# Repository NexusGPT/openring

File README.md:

<h1 align="center">OpenRing</h1>

<p align="center">
  <b>An open-source ring that records your meetings.</b><br>
  One joystick, a small screen, two microphones and its own storage, in a ring you wear on your index finger.
</p>

<p align="center">
  <a href="#what-it-is">What it is</a> ·
  <a href="#where-the-project-stands">Status</a> ·
  <a href="#inside-the-ring">Inside</a> ·
  <a href="#the-software">Software</a> ·
  <a href="#what-is-in-this-repository">Files</a> ·
  <a href="#check-it-yourself">Checks</a> ·
  <a href="#licence">Licence</a>
</p>

---

## What it is

OpenRing is the complete design of a meeting recorder that you wear as a ring:

- **Press and hold the joystick for one second** and the ring records. Hold again and it stops. Nothing else starts a recording: no voice trigger, no phone command, no always-on listening.
- **The screen shows that it records.** A red dot and a timer stay lit for the whole recording, so the people around you can see it.
- **The audio stays on the ring.** It is stored on the ring's own 4 GB memory and moves to your computer through the charging case over USB.
- **It also controls your devices.** Paired with up to three devices, the ring works as a Bluetooth keyboard, media remote and pointer, and it shows iPhone notifications.

Everything needed to build it is here: 3D models, wiring, parts lists, drawings, the assembly order, the behaviour specification and the ring's software with its tests.

## Where the project stands

> **This is a design, not a product. No ring has been built yet.**
> Every claim below says how it was checked. Nothing here has run on real hardware.
> State of 14 November 2026: an intermediate release, pushed while the work below is open.

| Part | State | How it was checked |
|---|---|---|
| Ring exterior, 7 sizes (US 7 to 13) | being rebuilt on the thin block (3.20 mm) for a flat cover glass over a custom full-face screen panel; a taller 4.17 mm exterior for a stock screen is kept as a fallback | 3D models per size, measured by script |
| Inside of the ring | designed for the thin block with a stock screen; the rebuild for the custom panel and the flat glass is in work | fit check per size on the earlier model |
| Charging case | designed; its fit to the ring with the flat glass is not redone yet | fit check against the earlier ring models |
| Circuit boards (17: the ring's main board, 14 band circuits for 7 sizes, 2 case boards) | **routed**. The main board is the thin ring's: screen connector on the under face, no soldered part on the screen face. The board for the 4.17 mm fallback is kept in `design/ecad/ring/pcb/fallback-417` | design rules check: 0 violations and 0 unconnected on each board; the main board's 8 limits for the antenna, crystal and USB lines are met |
| Wiring list (`design/wiring/product-wiring.csv`) | written: 66 conductors, each with both ends, its carrier and its cut length per size | a check compares the list with the boards and the netlists; an independent review found the list true (67 of 67 lines) |
| Joint table and build guide (`design/mfg/assembly/`) | written: 99 joints | **an independent review of 13 November failed the guide on 3 points, listed below; 1 is open, and the guide is behind the thin ring's main board** |
| Circuit simulation (`design/sim/circuit/`) | 13 tests pass | each test has a pass line written before the run and a faulty copy that must fail |
| Ring software: core, paired devices, control, iPhone services, screens, Android relay | written | simulated on the ring's chip model with real Bluetooth encryption |
| Ring software: recorder parts (microphones, storage, USB transfer, power) | written against simulated drivers | the full test run passes on the simulated board (732 of 732 test cases on each of two simulated targets); two independent reviews, the second passed it |
| Ring software: the real ring's board files | written: it builds for the real ring's board with the real drivers, and in a second form without the debug port | every chip pin is checked against the circuit's connection list, with deliberately wrong copies that must fail; four independent reviews, the fourth passed it; **nothing has run on hardware** (`firmware/docs/step7-report.md`) |
| Ring software: the screen's panel driver, the joystick's driver | **not written** | the panel driver needs the panel maker's answer |
| A working ring | **does not exist** | needs a development kit bench first, see `design/bench/` |

An independent review found three faults that stop a build from the files. Two are fixed in the guide; the first is open. They are written up in `design/wiring/wiring-review-4.md`:

1. **The body files are behind.** The body drawings still show the earlier block, without the two side slits the ribbons pass through and without the pocket of the custom screen panel. Open.
2. **Two ground joints per ribbon cannot be told apart by a meter.** The decision is to treat them as a spare pair; the guide now says what its test proves. Fixed.
3. **No test proved the two thermistor joints of the case.** A resistance check is added to the case board's tests. Fixed.

Four values need a measurement on the first built ring: the antenna match, the accuracy of the 32 MHz clock, the case's input current while a ring charges, and USB through the case's spring pins (`design/ecad/risk-review.md`).

## How you use it

<table>
  <tr>
    <td width="50%"></td>
    <td width="50%"></td>
  </tr>
</table>

The ring has **one control**: a round five-way joystick on the side of the band, under your thumb.

| You do | The ring does |
|---|---|
| Hold the centre for 1 second | starts a recording; hold again to stop |
| Short press while recording | marks a highlight |
| Push up, down, left, right | moves through the menu |
| Open a control mode | sends keys to the active device: media, slides, pointer, or accept and decline |

A vibration motor confirms the start and the stop.

## Inside the ring

| | |
|---|---|
| **Size** | block 29.3 x 14.75 x 3.85 mm on a band 8.0 mm wide and 2.6 mm thick |
| **Body** | titanium grade 5, gloss black |
| **Screen** | 0.95 inch AMOLED, 120 x 240 pixels, under a formed cover glass |
| **Main chip** | Nordic nRF54LM20A (Bluetooth LE) |
| **Power chip** | Nordic nPM1304 |
| **Microphones** | 2 x Knowles SPK0641HT4H-1, 16 kHz, 16 bit, two channels, stored raw |
| **Storage** | 4 GB, on the ring |
| **Battery** | a custom curved cell inside the band, 17.6 to 31.9 mAh depending on ring size |
| **Recording time** | 4.3 to 7.8 hours by ring size (calculated, not measured) |
| **Feedback** | vibration motor |
| **Charging** | 4 pads on the inside of the band, touched by 4 spring pins in the case |
| **Weight** | not known yet; body, joystick and motor alone come to 4.6 to 5.4 g |

The exploded view is an illustration from the project's own models. The reference is always the model and the parts list in `design/`.

## The screen

These 21 pictures come from the ring's own screen code. The code draws each screen on a simulated display, and a test reads the picture back from the display memory and checks it. The pictures are in `design/software/os/screens/`.

**Limit:** no real panel has shown them. The driver for the ring's panel is not written, because no ready driver exists for that panel.

## The charging case

<table>
  <tr>
    <td width="50%"></td>
    <td width="50%"></td>
  </tr>
</table>

A soft cube of 45.4 x 45.9 x 41.4 mm with a lid that swivels aside. The ring sits around a centre post. Four spring pins on the post touch the pads inside the band. The case charges the ring from its own 700 mAh cell and moves the recordings to a computer over USB-C.

One post holds all seven ring sizes. The fit check places the real ring model of every size in the case and measures every pin against its pad.

## The software

The ring runs a small firmware on Zephyr and the nRF Connect SDK. It is written to be proven without hardware: every step ends with tests on a simulated ring chip, and with deliberately broken copies that must fail.

| Step | What it does | State |
|---|---|---|
| 1. Core | the state machine and the joystick gestures of the behaviour specification | done, tests pass |
| 2. Devices and control | passkey pairing, three paired devices, keyboard, media and pointer control | done, tests pass |
| 3. iPhone | notifications with their actions, track and media commands, time | done, tests pass |
| 4. Screens | the 21 screens, the menu, the notification list, the control and device screens | done, tests pass |
| 5. Android relay | a small service on the ring that takes notifications from a helper app, and the written specification for that app | done, tests pass |
| 6. Recorder | microphones, storage, USB transfer, power, factory tests, against simulated drivers | written and reviewed; the fixes of the last review are in, their full test run pending |
| 7. Board | the real ring's board files | not started |

What works per device, by design:

| Device | Control by the ring | Notifications on the ring |
|---|---|---|
| iPhone | yes | yes |
| Android | yes | yes on the ring side; needs a helper app on the phone (specified in `design/software/os/android-helper-spec.md`, not built) |
| Mac | yes | no supported way was found |

**Honest limit:** the tests use stand-in devices written for this project. Nothing has been tried against a real iPhone, Android phone or Mac.

## What is in this repository

| Folder | What it holds |
|---|---|
| `requirements.md` | what the ring must do, with every later change and its reason |
| `design/architecture.md` | the design record: every decision, in order |
| `design/bom.csv` | the ring's parts list, with maker part numbers |
| `design/ecad/` | wiring diagram, netlist and circuit board files (KiCad) |
| `design/wiring/` | every conductor of the product in one list, its drawing, the decisions and the independent wiring reviews |
| `design/sim/` | the circuit simulation bench |
| `design/mech/` | the inside model of the ring and its fit check |
| `design/look/` | the exterior model, one file per ring size |
| `design/mfg/` | maker files (STEP, STL), drawings, one specification page per custom part, the assembly order |
| `design/case/` | the charging case: model, parts list, wiring, fit check |
| `design/firmware.md` | the behaviour specification the software follows |
| `design/bench/` | the plan for a desk prototype from development kits |
| `design/review/` | three independent reviews of the design, with their findings |
| `firmware/` | the ring's software, its tests and the build scripts |
| `explorer/` | a browser app to look through the design |
| `LICENSES/`, `LICENSE.md`, `NOTICE.md` | the licences and the third-party notice |

Maker datasheets are not included. `design/datasheets/README.md` lists each bought part with its maker and part number.

## Check it yourself

The design ships with its own checks. Each one reads the design files and fails when they disagree with each other.

These run from this repository alone:

```sh
python3 design/tools/check_bom.py          # parts list against the wiring and the model
python3 design/mfg/tools/check_docs.py     # maker specification pages
python3 design/case/check_case_docs.py     # case documents
python3 tools/check_public.py              # this repository holds no private or third-party file
```

These four also read the makers' own datasheets, which are not in this repository (their makers own them). They stop with "cannot read" or "no file" until you download the documents listed in `design/datasheets/README.md` and put them where each check names them:

```sh
python3 design/ecad/ring/check_netlist.py         # wiring rules, against the makers' pin tables
python3 design/firmware-check.py                  # behaviour specification
python3 design/mfg/assembly/check_assembly.py     # assembly order and its citations
python3 design/bench/check_bench.py design/bench/bench-plan.md design/bom.csv
```

All seven passed on the full project before the maker documents were taken out for this release.

The 3D model checks (`design/mech/thin/check_thin.py`, `design/case/case_check.py`) need the Python package `build123d` and take 20 to 60 minutes each.

To build and test the software, read `firmware/README.md`. It needs Linux and Nordic's toolchain; the chip simulation does not run on macOS.

## What is not done

- The first fault above (the body files) is open.
- The inside model, the body maker files, the case fit and the pictures of this page still show the thin block with a stock screen under a formed glass (3.85 mm on this page's table). The design moves to a custom screen panel that fills the face, under a flat glass, on the same thin block. The requirement page for panel makers is `design/mfg/specs/screen-panel-custom.md`; no maker has answered.
- The build guide and its joint table still describe a second soldering pass for the main board's screen face. The thin ring's board has no soldered part there, so that pass is no longer needed; the guide's rework is open.
- No part has been ordered, measured or assembled.
- The spring pin of the case and the thin walls of its pin holder are not confirmed by a maker.
- Battery life, radio range, sound quality, water resistance and weight are calculated or unknown. None is measured.
- The software has no panel driver and no board files for the real ring yet. The Android helper app is specified and not built.

If you build any of it, measure something, or find a mistake, open an issue. That is why the design is public.

## Licence

OpenRing is open hardware and open software:

| What | Licence |
|---|---|
| Hardware design: 3D models, wiring, circuit board, parts lists, drawings | CERN-OHL-S 2.0 (share-alike) |
| Software: `firmware/`, `explorer/` and every script | Apache 2.0 |
| Documents and pictures | CC BY 4.0 |

The licence texts are in `LICENSES/`. Details per folder are in [LICENSE.md](LICENSE.md). Third-party software and parts keep their own licences, see [NOTICE.md](NOTICE.md).

## About the name

This project is not related to other projects with a similar name, among them the research app repository `thuhci/OpenRing` and the hardware project `stawiski/open-ring`.

## How this was made

The pictures on this page are rendered from the project's own 3D models. The design files, the checks and the software were produced with AI assistance and reviewed by independent AI reviewers; their reports are in `design/review/` and `firmware/docs/`. Treat every number as a design value until someone measures it.

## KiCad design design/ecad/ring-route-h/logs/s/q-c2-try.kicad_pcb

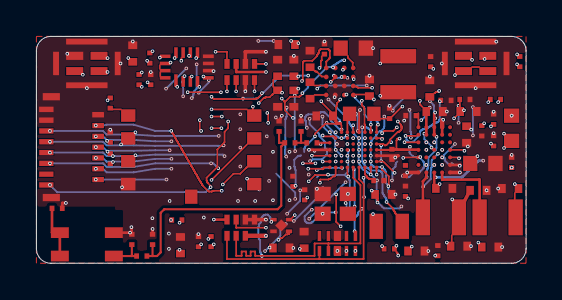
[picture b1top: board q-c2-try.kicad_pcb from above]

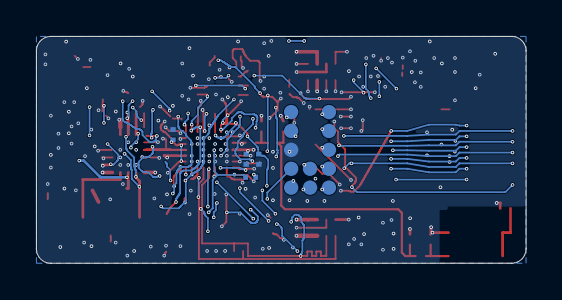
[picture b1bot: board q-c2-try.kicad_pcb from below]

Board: 4 copper layers, 27.2 x 12.6 mm, 99 parts (16 on the bottom side), 84 nets.

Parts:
ANT1: 2450AT18D0100001E; ANT_Johanson_2450AT18D0100001E_3.2x1.6
C1, C2, C5, C61, C72, C80, C81, C82: 100nF; Chip_0201
C3: 1.2pF; Chip_0201
C4, C22, C25, C74, C75, C78, C79, C83, C90: 10uF; Chip_0402
C6: 4.7uF; Chip_0201
C7, C10, C14: 2.2uF; Chip_0201
C11, C21, C26, C27, C84: 4.7uF; Chip_0402
C12: 0.5pF; Chip_0201
C13, C89: DNP; Chip_0201
C23, C60, C85: 2.2uF; Chip_0402
C24, C88: 10uF; Chip_0603
C28, C29: 22uF; Chip_0402
C31, C32: 1uF; Chip_0201
C35, C36: 1nF C0G; Chip_0402
C71: 1.0uF 25V; Chip_0402
C73: 1.0uF; Chip_0201
C76, C77: 1.0nF; Chip_0201
C86, C87: 1.0uF; Chip_0402
FB1: 120R@100MHz; Chip_0201
J1: FH35C-15S-0.3SHW(50); FPC_Hirose_FH35C-15S-0.3SHW
J_BAND_A: flex tail A (joystick side) 8 pads; J_BAND_A_BOARD
J_BAND_B: flex tail B (other side) 7 pads; J_BAND_B_BOARD
L1: 4.7uH; L_TDK_MLZ1608_1.6x0.8
L2: 3.6nH; Chip_0201
L3: 4.7nH; Chip_0201
L4: 3.3nH; Chip_0201
L10, L71, L72: 2.2uH; L_Murata_1269AS-H_2.5x2.0
LT1: 0R; Chip_0201
R1: 2.2R; Chip_0603
R2: 220R; Chip_0201
R31, R32, R61: 100R; Chip_0201
R57, R58: 4.7k; Chip_0201
R60, R63, R64, R65, R71: 47k; Chip_0201
R62, R66: 100k; Chip_0201
R72: 150k; Chip_0201
R73: 330k; Chip_0201
TP1, TP3, TP4, TP5, TP6, TP12, TP14, TP15, TP17, TP18, TP19, TP21: pad; TESTPAD_0.8
U1: nRF54LM20A; WLCSP-61_nRF54LM20A-CAAA
U2: nPM1304; WLCSP-35_nPM1304-CAAA
U3: CSNP32GCR01-BOW; LGA-9_CSNP32GCR01-BOW_8.0x6.2
U4: SGM38046; WLCSP-16_SGM38046_2.0x2.0_P0.5
U5, U6: SPK0641HT4H-1; LGA-8_Knowles_SPK0641HT4H-1_3.0x4.0
U9: TPD4E05U06; USON-10_TPD4E05U06DQA
U10: SN74AXC4T774; UQFN-16_SN74AXC4T774RSV_1.8x2.6
U11: TLV75530P 3.0V; X2SON-4_TLV755xxPDQN_1.0x1.0
X1: 32MHz; XTAL_Kyocera_CX2016DB_2.0x1.6
X2: 32.768kHz; XTAL_TXC_9HT11_2.0x1.2

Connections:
ANT1_NODE: L2.1, U1.C1
ANT2_NODE: C3.1, L2.2, L3.1
ANT3_NODE: C12.1, C89.1, L3.2, L4.1
ANT_TRIM: ANT1.2, ANT1.3, LT1.1
BTN_REC: J_BAND_A.5, U1.H2
DBG_TX: TP1.1, U1.B4
DCC: L1.1, U1.A5
DECA: C7.1, C14.1, FB1.2, U1.A8, U1.B2
DECD: C6.1, FB1.1, L1.2, U1.A6
ELVDD: C25.1, J1.2, U4.D3
ELVSS: C28.1, C29.1, J1.1, U4.D4
GND: ANT1.4, C1.2, C2.2, C3.2, C4.2, C5.2, C6.2, C7.2, C10.2, C11.2, C12.2, C13.2, C14.2, C21.2, C22.2, C24.2, C25.2, C26.2, C27.2, C28.2, C29.2, C31.2, C32.2, C35.2, C36.2, C60.2, C61.2, C71.2, C72.2, C73.2, C74.2, C75.2, C76.2, C77.2, C78.2, C79.2, C80.2, C81.2, C82.2, C83.2, C84.2, C85.2, C86.2, C87.2, C88.2, C89.2, C90.2, J1.13, J1.14, J1.15, J1.MP, J_BAND_A.6, J_BAND_A.8, J_BAND_B.2, J_BAND_B.7, LT1.2, R2.2, R62.2, R66.2, R71.2, R72.2, R73.2, TP18.1, U1.A7, U1.D3, U1.E1, U1.F10, U2.A6, U2.A7, U2.E7, U3.4, U4.A3, U4.B2, U4.B3, U5.3, U5.5, U5.6, U5.7, U5.8, U6.5, U6.6, U6.7, U6.8, U9.3, U9.8, U10.6, U10.7, U10.8, U11.2, U11.5, X1.2
JOY_DOWN: J_BAND_A.2, U1.G2
JOY_LEFT: J_BAND_A.3, U1.G1
JOY_RIGHT: J_BAND_A.4, U1.G10
JOY_UP: J_BAND_A.1, U1.H1
LCD_CS: J1.9, U1.F7
LCD_DCX: J1.11, U1.G7
LCD_MOSI: J1.12, U1.G8
LCD_RST: J1.8, U1.H5
LCD_SCK: J1.10, U1.G9
LCD_TE: J1.7, U1.F4
MIC1_DATA: R31.1, U5.1
MIC2_DATA: R32.1, U6.1
MIC_A_CLK: U1.F1, U5.2, U6.2
MIC_A_DATA: R31.2, R32.2, U1.F2
MIC_B_DATA: TP21.1, U1.D7
MOTOR: R61.1, U1.F6
MOT_EN: R61.2, R62.1, U11.3
NRESET: TP5.1, U1.E2
NTC: J_BAND_B.3, U2.D3
OLED_PWR_EN: R66.1, U1.F9, U4.C2
PMIC_INT: U1.D8, U2.D6
PMIC_SCL: R58.1, U1.E7, U2.E3
PMIC_SDA: R57.1, U1.B8, U2.E5
RF_FEED: ANT1.1, C13.1, L4.2
SDC_CS: R65.1, U3.2, U10.10
SDC_MISO: R60.1, U3.6, U10.9
SDC_MOSI: U3.5, U10.11
SDC_SCK: U3.3, U10.12
SD_CS: U1.D9, U10.3
SD_DAT1: R63.1, U3.7
SD_DAT2: R64.1, U3.1
SD_MISO: U1.D10, U10.4
SD_MOSI: U1.B10, U10.2
SD_SCK: U1.A9, U10.1
SGM_AVDD: C26.1, U4.D2
SGM_AVIN: C22.1, U4.A2
SGM_C1N: C23.2, U4.B4
SGM_C1P: C23.1, U4.A4
SGM_SW1: L10.1, U4.B1
SGM_SW2: L10.2, U4.C1
SGM_VON: C27.1, U4.C4
SGM_VOUT: C24.1, U4.D1
SHPHLD: TP19.1, U2.D4
SPARE_P1_00: TP6.1, U1.H10
SPARE_P2_00: TP12.1, U1.A10
SPARE_P3_03: TP14.1, U1.F5
SPARE_P3_04: TP15.1, U1.G5
SW1: L71.1, U2.B7
SW2: L72.1, U2.D7
SWDCLK: TP3.1, U1.D5
SWDIO: TP4.1, U1.E4
SWIRE: J1.6, U4.C3
TXRTUNE: R2.1, U1.G6
U1_VBUS: C11.1, R1.2, U1.H9
USB_DN: J_BAND_B.5, U1.H6, U9.2
USB_DP: J_BAND_B.6, U1.H7, U9.1
VBAT: C21.1, C83.1, C85.1, J_BAND_B.1, U2.D1, U2.D2, U4.A1, U11.4
VBUS: C71.1, C72.1, J_BAND_B.4, R1.1, R73.1, U2.B1, U2.B2, U9.4, U9.5
VBUSOUT: C73.1, U2.C3
VDD_1V8: C1.1, C2.1, C4.1, C5.1, C78.1, C80.1, C81.1, J1.5, L71.2, R57.2, R58.2, TP17.1, U1.A4, U1.E10, U2.B4, U2.B6, U2.E4, U10.5, U10.14, U10.15, U10.16
VDD_3V0: C79.1, C90.1, J1.4, L72.2, U2.B5, U2.C6
VDD_MIC: C31.1, C32.1, C35.1, C36.1, C86.1, U2.A4, U5.4, U6.3, U6.4
VDD_SD: C60.1, C61.1, C82.1, C87.1, R60.2, R63.2, R64.2, R65.2, U2.A5, U3.8, U10.13
VDD_USB_3V3: C10.1, U1.H8
VMOT: C84.1, J_BAND_A.7, U11.1
VSET1: R71.1, U2.E2
VSET2: R72.1, U2.E1
VSYS: C74.1, C75.1, C76.1, C77.1, C88.1, U2.C1, U2.C2, U2.C7
XC1: U1.A2, X1.1
XC2: U1.A1, X1.3
XL1: U1.B6, X2.1
XL2: U1.B7, X2.2

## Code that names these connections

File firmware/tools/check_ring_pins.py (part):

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A U1 row whose net is in no list fails too (UNLISTED). Last line: "check_ring_pins: RESULT PASS ..." (exit 0) or
"check_ring_pins: RESULT FAIL ..." (exit 1). Exit 2: the inputs could not be read.

--production: the production build (fix round 2, S7R-08): DBG_TX must be a gpio hog on its netlist pin, an input with
the chip's pull-down and no other compared flag (design/firmware.md l.1061), and uart20 must not name it.

--source-netlist: when that file exists (the design copy, design/ecad/ring/netlist.csv, present on the Mac but not on
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#   psel: the node's pin-control states: the <function> in every state (default, sleep) must name the pin
#   fixed: a pin with one function on this chip: the node must exist and be enabled; the pin comes from the chip
SIGNALS = {
    "BTN_REC": ("gpio", "ring_btn_rec", "gpios"),
    "JOY_UP": ("gpio", "ring_joy_up", "gpios"),
    "JOY_DOWN": ("gpio", "ring_joy_down", "gpios"),
    "JOY_LEFT": ("gpio", "ring_joy_left", "gpios"),
    "JOY_RIGHT": ("gpio", "ring_joy_right", "gpios"),
    "MOTOR": ("gpio", "ring_motor", "gpios"),
    "LCD_CS": ("gpio", "spi21", "cs-gpios"),
    "LCD_DCX": ("gpio", "ring_lcd_dbi", "dc-gpios"),
    "LCD_RST": ("gpio", "ring_lcd_dbi", "reset-gpios"),
    "LCD_TE": ("gpio", "ring_lcd_dbi", "te-gpios"),
    "OLED_PWR_EN": ("gpio", "/zephyr,user", "oled-pwr-en-gpios"),
    "PMIC_INT": ("gpio", "ring_pmic", "host-int-gpios"),
    "SD_CS": ("gpio", "spi00", "cs-gpios"),
    "MIC_B_DATA": ("gpio", "/zephyr,user", "mic-b-data-gpios"),
    "SPARE_P1_00": ("gpio", "/zephyr,user", "spare-p1-00-gpios"),
    "SPARE_P2_00": ("gpio", "/zephyr,user", "spare-p2-00-gpios"),
    "SPARE_P3_03": ("gpio", "/zephyr,user", "spare-p3-03-gpios"),
    "SPARE_P3_04": ("gpio", "/zephyr,user", "spare-p3-04-gpios"),
    "DBG_TX": ("psel", "uart20", "UART_TX"),
    "SD_SCK": ("psel", "spi00", "SPIM_SCK"),
    "SD_MOSI": ("psel", "spi00", "SPIM_MOSI"),
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    "GND": "ground",
    "VDD_1V8": "supply",
    "VDD_USB_3V3": "the chip's USB regulator output (DECUSB), a capacitor only",
    "DCC": "the DC/DC converter's inductor L1 (vregmain's mode is set in the devicetree, no pin)",
    "DECA": "decoupling",
    "DECD": "decoupling",
    "TXRTUNE": "radio tuning resistor R2",
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# expected GPIO flags of the GPIO-kind signals: (names of the gpio.h flags that must be set, source); None = no source
# states the flags, printed as "no source" and not compared. Only ACTIVE_LOW, PULL_UP and PULL_DOWN are compared.
FLAGS = {
    "BTN_REC": (("GPIO_PULL_UP", "GPIO_ACTIVE_LOW"), "design/firmware.md l.82"),
    "JOY_UP": (("GPIO_PULL_UP", "GPIO_ACTIVE_LOW"), "design/firmware.md l.82"),
    "JOY_DOWN": (("GPIO_PULL_UP", "GPIO_ACTIVE_LOW"), "design/firmware.md l.82"),
    "JOY_LEFT": (("GPIO_PULL_UP", "GPIO_ACTIVE_LOW"), "design/firmware.md l.82"),
    "JOY_RIGHT": (("GPIO_PULL_UP", "GPIO_ACTIVE_LOW"), "design/firmware.md l.82"),
    "MOTOR": ((), "design/firmware.md l.83 (output, active high)"),
    "PMIC_INT": ((), "design/firmware.md l.865 (active high)"),
    "OLED_PWR_EN": ((), "design/firmware.md l.381 (high = screen supply on)"),
    "LCD_RST": (("GPIO_ACTIVE_LOW",), "design/firmware.md l.381 (low = reset, high = run)"),
    "LCD_TE": ((), "design/firmware.md l.84 (input, rising edge)"),
    "SD_CS": (("GPIO_ACTIVE_LOW",), "design/firmware.md l.506 (SD_CS high when idle)"),
    "LCD_CS": None,
    "LCD_DCX": None,
    "MIC_B_DATA": None,
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    production = "--production" in argv
    signals = dict(SIGNALS)
    if production:
        signals["DBG_TX"] = ("hog", "gpio-hog", "input, GPIO_PULL_DOWN")
    src = None
    if "--source-netlist" in argv:
        src = argv[argv.index("--source-netlist") + 1]
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
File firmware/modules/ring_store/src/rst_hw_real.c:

/*
 * rst_hw_real.c: the real card and storage bus for the storage part (software step 6, unit U2). Built only where the
 * simulated drivers are off (the development kit build, decision D15). It is NOT PROVEN: no card and no SPI exist in
 * any test of step 6 (plan section 7, item 1). Where the devicetree has no `spi00` node the file registers nothing and
 * every card call keeps answering -ENODEV (the "absent" instance of ring_rhw).
 * Kit calls used: the disk access API (init, deinit and sector count through ioctl, read, write) and device power
 * management (suspend, resume). No pin is named here.
 */
#include <errno.h>

#include <zephyr/device.h>
#include <zephyr/devicetree.h>
#include <zephyr/drivers/gpio.h>
#include <zephyr/drivers/pinctrl.h>
#include <zephyr/init.h>
#include <zephyr/pm/device.h>
#include <zephyr/storage/disk_access.h>

#include <ring_rhw/rhw.h>

/* what the full-run stage "recorder-product-drivers" prints: whether the real calls were compiled */
#if DT_NODE_EXISTS(DT_NODELABEL(spi00)) && defined(CONFIG_DISK_ACCESS)
const bool rst_hw_real_compiled = true;

#define RST_DISK_NAME "SD"

static int r_init(void)
{
	return disk_access_ioctl(RST_DISK_NAME, DISK_IOCTL_CTRL_INIT, NULL);
}

static int r_deinit(void)
{
	return disk_access_ioctl(RST_DISK_NAME, DISK_IOCTL_CTRL_DEINIT, NULL);
}

static int r_read(uint32_t lba, uint8_t *buf, uint32_t count)
{
	return disk_access_read(RST_DISK_NAME, buf, lba, count);
}

static int r_write(uint32_t lba, const uint8_t *buf, uint32_t count)
{
	return disk_access_write(RST_DISK_NAME, buf, lba, count);
}

static int r_count(uint32_t *out)
{
	return disk_access_ioctl(RST_DISK_NAME, DISK_IOCTL_GET_SECTOR_COUNT, out);
}

static const struct rhw_disk_api real_disk = {
	.init = r_init, .deinit = r_deinit, .read = r_read, .write = r_write, .sector_count = r_count,
};

/* The card's four lines and VDD_SD (FW l.506: no storage line driven high while VDD_SD is off). Step 7 fix round 3
 * (S7T-01): the lines' safe state is tied to the supply, not to the bus driver's state. lines_safe() makes the four
 * lines safe with no condition: SD_CS (a GPIO of spi00, cs-gpios, outside every pin state) disconnected through the
 * GPIO API, and spi00's own "sleep" pin state (SD_SCK, SD_MOSI, SD_MISO inputs with no pull) applied through the pin
 * control API on spi00's devicetree configuration, not through the SPI driver. Both need only the devicetree, not the
 * device: PINCTRL_DT_DEV_CONFIG_GET is the address of a structure PINCTRL_DT_DEFINE builds from the devicetree
 * (zephyr/include/zephyr/drivers/pinctrl.h l.265, l.242 to 248) and pinctrl_apply_state writes the pins directly
 * (l.345 to 357, l.319 to 332: pinctrl_configure_pins), so it is legal whether spi00 was never initialised, is active,
 * is suspended or failed its init. The kit's SPIM driver drives SD_CS high from its init (spi_nrfx_spim_common_init
 * l.771, cs_init l.678) and leaves it so on suspend (cs_put l.571).
 *
 * The hook the storage part calls before VDD_SD goes off, b_suspend(), is one wrapper that always ends in
 * lines_safe(); b_resume() calls lines_safe() on every failure. tools/build_all.sh stage ring-lines-safe checks that
 * shape. On the ring, spi00, its slot and its disk carry zephyr,deferred-init (fix round 2): nothing drives the lines
 * before the first power-on, whose first resume initialises the three (after VDD_SD is on and 1 ms, rst.c l.345 to
 * 349). */
BUILD_ASSERT(DT_NODE_HAS_PROP(DT_NODELABEL(spi00), cs_gpios), "spi00 needs cs-gpios (the card's SD_CS)");
BUILD_ASSERT(DT_PINCTRL_HAS_NAME(DT_NODELABEL(spi00), sleep), "spi00 needs a sleep pin state (the card's lines off)");
/* without device power management Zephyr leaves every "sleep" pin state out of the build (pinctrl.h,
 * PINCTRL_SKIP_SLEEP), and pinctrl_apply_state(..., PINCTRL_STATE_SLEEP) would find no state */
BUILD_ASSERT(IS_ENABLED(CONFIG_PM_DEVICE), "lines_safe() needs CONFIG_PM_DEVICE for spi00's sleep pin state");

#define RST_BUS DEVICE_DT_GET(DT_NODELABEL(spi00))
static const struct gpio_dt_spec sd_cs = GPIO_DT_SPEC_GET_BY_IDX(DT_NODELABEL(spi00), cs_gpios, 0);
PINCTRL_DT_DEFINE(DT_NODELABEL(spi00));
static const struct pinctrl_dev_config *const spi00_pins = PINCTRL_DT_DEV_CONFIG_GET(DT_NODELABEL(spi00));

/* The four lines safe: no condition, no device state read. */
static int lines_safe(void)
{
	int c = gpio_pin_configure_dt(&sd_cs, GPIO_DISCONNECTED);
	int p = pinctrl_apply_state(spi00_pins, PINCTRL_STATE_SLEEP);

	return c != 0 ? c : p;
}

#if DT_PROP_OR(DT_NODELABEL(spi00), zephyr_deferred_init, 0)
#define RST_SLOT_NODE DT_COMPAT_GET_ANY_STATUS_OKAY(zephyr_sdhc_spi_slot)
#define RST_DISK_NODE DT_COMPAT_GET_ANY_STATUS_OKAY(zephyr_sdmmc_disk)
/* the slot and the disk need spi00 at their init (sdhc_spi_init: device_is_ready(spi_dev)), so they must wait too */
BUILD_ASSERT(DT_PROP_OR(RST_SLOT_NODE, zephyr_deferred_init, 0) && DT_PROP_OR(RST_DISK_NODE, zephyr_deferred_init, 0),
	     "spi00 is zephyr,deferred-init: its zephyr,sdhc-spi-slot and zephyr,sdmmc-disk nodes must be too");
static bool bus_up;

/* The first power-on: initialise spi00, the slot and the disk in order. A failed init leaves the device initialised
 * with an error (zephyr/kernel/device.c: init_res set, then initialized = true; device_init answers -EALREADY to a
 * second call), so success is device_is_ready() (initialized && init_res == 0) of all three, not device_init's
 * return; else bus_up stays false and the caller's wrapper makes the lines safe. */
static int bus_first_init(void)
{
	const struct device *const devs[] = { RST_BUS, DEVICE_DT_GET(RST_SLOT_NODE), DEVICE_DT_GET(RST_DISK_NODE) };

	for (size_t i = 0; i < ARRAY_SIZE(devs); i++) {
		(void)device_init(devs[i]);
	}
	for (size_t i = 0; i < ARRAY_SIZE(devs); i++) {
		if (!device_is_ready(devs[i])) {
			return -ENODEV;
		}
	}
	bus_up = true;
	return 0;
}
#else
static bool bus_up = true;

static int bus_first_init(void)
{
	return 0;
}

/* not deferred (another board): the kit's spi00 init drove SD_CS high at boot; make the lines safe after the kit's
 * devices */
static int rst_hw_real_lines_boot(void)
{
	return lines_safe();
}
SYS_INIT(rst_hw_real_lines_boot, POST_KERNEL, 99);
#endif

/* The driver's own suspend when the bus is up (so its state stays right); nothing when it never came up. */
static int suspend_inner(void)
{
	if (!bus_up) {
		return 0;
	}

	int r = pm_device_action_run(RST_BUS, PM_DEVICE_ACTION_SUSPEND);

	return r == -EALREADY ? 0 : r;
}

/* The first power-on initialises the bus; later ones drive SD_CS inactive and resume the driver (VDD_SD is on). */
static int resume_inner(void)
{
	if (!bus_up) {
		return bus_first_init();
	}

	int c = gpio_pin_configure_dt(&sd_cs, GPIO_OUTPUT_INACTIVE);

	if (c != 0) {
		return c;
	}
	return pm_device_action_run(RST_BUS, PM_DEVICE_ACTION_RESUME);
}

/* The hook before VDD_SD goes off: always ends in lines_safe() (checked by stage ring-lines-safe). */
static int b_suspend(void)
{
	int r = suspend_inner();
	int s = lines_safe();

	return r != 0 ? r : s;
}

/* Resume: on every failure the lines are made safe (checked by stage ring-lines-safe). */
static int b_resume(void)
{
	int r = resume_inner();

	if (r != 0) {
		(void)lines_safe();
	}
	return r;
}

static const struct rhw_sdbus_api real_sdbus = { .suspend = b_suspend, .resume = b_resume };

static int rst_hw_real_register(void)
{
	int r = rhw_register_disk(&real_disk);

	return r != 0 ? r : rhw_register_sdbus(&real_sdbus);
}

SYS_INIT(rst_hw_real_register, APPLICATION, 50);
#else
const bool rst_hw_real_compiled = false;
#endif

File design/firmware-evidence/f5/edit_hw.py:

import sys
p = sys.argv[1]
s = open(p, encoding="utf-8").read()
reps = [
("Status in F4 of the issues raised in F1 and F2, after the lead's decisions and architecture A5-draft (H8 changes in F4: the charger switch-on is no longer blocked, only the current is; H14 and H15 are new):\n\n| Id | Conflict | Status in F3 | Firmware choice | Who acts |",
 "Status in F5 of the issues raised in F1 to F4, after architecture A5-draft sections 17.13 to 17.23 (H8 and H9 close in F5; H16 to H19 are new):\n\n| Id | Conflict | Status | Firmware choice | Who acts |"),
("| 1.280 MHz, ratio 80, exactly 16 kHz, inside the 1.2 to 1.65 MHz normal mode [DS] | bench B2 measures the current |",
 "| 1.280 MHz, ratio 80, exactly 16 kHz, inside the 1.000 to 4.800 MHz performance mode of the microphone of 17.19 [DS line 95] | bench B2 measures the current |"),
("on the main board beside the cell, on the nPM1300 NTC pin (lead's note); sch-notes section 3 still lists the RT1 value as OPEN 12.2 | charger limits of section 8.1 | schematic owner: write 10 kilo-ohm and the part for RT1; its beta sets `thermistor-beta` |",
 "on the power chip's NTC pin (nPM1304 ball D3, netlist.csv) | charger limits of section 8.1 | schematic owner: the RT1 part, with B25/50 = 3,380 K for the chip's 10 kilo-ohm type [NPM p24] |"),
("| closed: PMIC_INT on nPM1300 GPIO0, SHPHLD on test pad TP19 (sch-notes sections 2 and 8) | `pmic-int-pin = 0`; wake from `SHIP` and `OFF` only by VBUS | Nordic datasheet (action 12.2) confirms the VBUS exit |",
 "| closed: PMIC_INT on nPM1304 GPIO0 (ball D6), SHPHLD on test pad TP19 (netlist.csv); VBUS above 3.9 V ends ship mode [NPM p116, p17] | `pmic-int-pin = 0`; wake from `SHIP` and `OFF` only by VBUS | none |"),
("| H7 | The motor draws below 80 mA running and up to 175 mA at each start (architecture 17.16) from a cell of 20 to 27 mAh: 2.9 to 3.9 C running, 6.4 to 8.6 C at the start. (Before 2026-11-11: 85 mA, 15 to 20 mAh, 4.3 to 5.7 C.) No cell discharge limit and no protection-circuit trip current is in the architecture. | open | the patterns are unchanged; B15 and B5 stop recording before the cell is low, but a trip of the protection circuit at 85 mA would cut power in a pulse |",
 "| H7 | The motor draws below 80 mA running and up to 175 mA at each start (architecture 17.16), now straight from the cell through U11 (17.22): 4.4 C running and 9.6 C at the start on the smallest cell, 18.2 mAh, and 2.4 C and 5.3 C on the largest, 32.9 mAh [CALC, section 3.1]. A start takes up to 228 mA from the cell with every other load on (17.22). No cell discharge limit and no protection-circuit trip current is on file. | open | the patterns are unchanged; B15 and B5 stop recording before the cell is low, but a trip of the protection circuit in a motor start would cut power in a pulse |"),
("| H8 | The nPM1300's lowest charge current, 32 mA, is above 1 C for this cell, 1.6 to 2.1 C on 15 to 20 mAh (architecture 17.5, 17.10, S12). | open, blocked (current only) | `CHARGE_CURRENT` has no value and the build fails while it is unset; the charger is on whenever VBUS is present (R-CHG); the charging states stay; T-CHARGE has no pass limit and fails when the charger is off with VBUS present | Grepow (highest charge current), then Nordic or a second charger part (S12) |",
 "| H8 | F4: the power chip of F4 could not charge under 32 mA, above 1 C of the cell. | closed by architecture 17.13: the nPM1304 charges from 4 mA [NPM p24] | `CHARGE_CURRENT` = 15 mA, 0.82 C of the smallest cell; T-CHARGE passes at 13.5 to 16.5 mA | Grepow states the cell's own limit (S12); the value changes in one place |"),
("| H9 | The IM68D128B has no datasheet in `design/datasheets/` (architecture section 2: figures from the IM68D121J brief). | open | 1.280 MHz, ratio 80 and the 50 ms discard stay as in F2, from the IM73D122V01 datasheet | design lead: save the IM68D128B datasheet, then check section 10.5 item 24 |",
 "| H9 | F4: the microphone had no datasheet on disk. | closed by architecture 17.19: the Knowles SPK0641HT4H-1 has a datasheet copy | 1.280 MHz, ratio 80 and the 50 ms discard, now from that copy (sections 4.1, 4.5) | Knowles or a distributor confirms the part is made (S23) |"),
("| open | RT1 on the nPM1300 NTC pin, 10 kilo-ohm, limits of section 8.1 |",
 "| open | RT1 on the nPM1304 NTC pin, 10 kilo-ohm, limits of section 8.1 |"),
("| open | F4 follows 17.11 (later sections win); BTN_REC is the centre switch in case `SW2` | architecture owner: rewrite those lines |",
 "| open | F4 and F5 follow 17.11 (later sections win); BTN_REC is the centre switch in case `SW2` | architecture owner: rewrite those lines |\n"
 "| H16 | The brief and architecture 17.19 ask the gain to change by 11 dB for the more sensitive microphone. At -11 dB the microphone's own noise, -26 - 64.5 - 11 = -101.5 dBFS(A), falls under the noise of a 16-bit sample, -(6.02 x 16 + 1.76) = -98.1 dBFS; the stored signal-to-noise at 94 dB SPL drops from about 63.8 dB at 0 dB gain to about 59.5 dB [CALC, `design/firmware-f5-notes.md`; assumes the PDM truncates to 16 bits after the gain; not A-weighted]. At 0 dB the store clips at 120 dB SPL, the microphone's own overload point. | open | gain -11 dB (0x12) as the brief asks; one constant | the lead: keep -11 dB or go back to 0 dB; bench B7 can measure the floor |\n"
 "| H17 | Architecture section 3 still says \"the power chip stops discharge at 3.1 V\" and section 2 and 3 still name the older power chip; motor-drive.md section 2.4 uses that 3.1 V. The nPM1304 specification read gives a power-fail reset at VSYSPOF, 2.7 V by default (2.5 to 3.4 V) [NPM p109], and a brownout at 2.4 V [NPM p29]; no 3.1 V cut-off was found. | open | B2 at 3.30 V and B5 at 3.45 V stay; VSYSPOF stays at its default (section 8.7) | architecture owner: rewrite section 3; the cell maker: the protection circuit's undervoltage limit (S12) |\n"
 "| H18 | Architecture 17.15 and 17.17 give the recording hours at 4.0 mA (4.5 to 8.2 hours across US 7 to 13); with the microphones of 17.19 the current is 4.1 mA and the hours are 4.4 to 8.0 [CALC, section 8.5]. | open | F5 uses 4.1 mA | architecture owner: update 17.17 and the key numbers |\n"
 "| H19 | Assembly step 25 reads the boot count after FACTORY ENTER and expects the same count after VBUS is removed and put back; removing VBUS in `FACTORY_TEST` reboots the ring (section 1.2), so the count rises by 1. Its stated reason (a motor start over the 100 mA limit) is also out of date since 17.22, and its step 2 still lists Q1 and D1 (17.23 says 17.22 wins). | open | section 9.3 sends FACTORY_EXIT before the count is read; the check stays as a proof of no reset | assembly owner: update steps 2 and 25 |"),
]
bad = 0
for a, b in reps:
    n = s.count(a)
    print(n, a[:70])
    if n == 1:
        s = s.replace(a, b)
    else:
        bad += 1
lines = s.rstrip("\n").split("\n")
assert lines[-1].startswith("RESULT:")
lines[-1] = sys.argv[2]
s = "\n".join(lines) + "\n"
open(p, "w", encoding="utf-8").write(s)
print("not applied:", bad)
